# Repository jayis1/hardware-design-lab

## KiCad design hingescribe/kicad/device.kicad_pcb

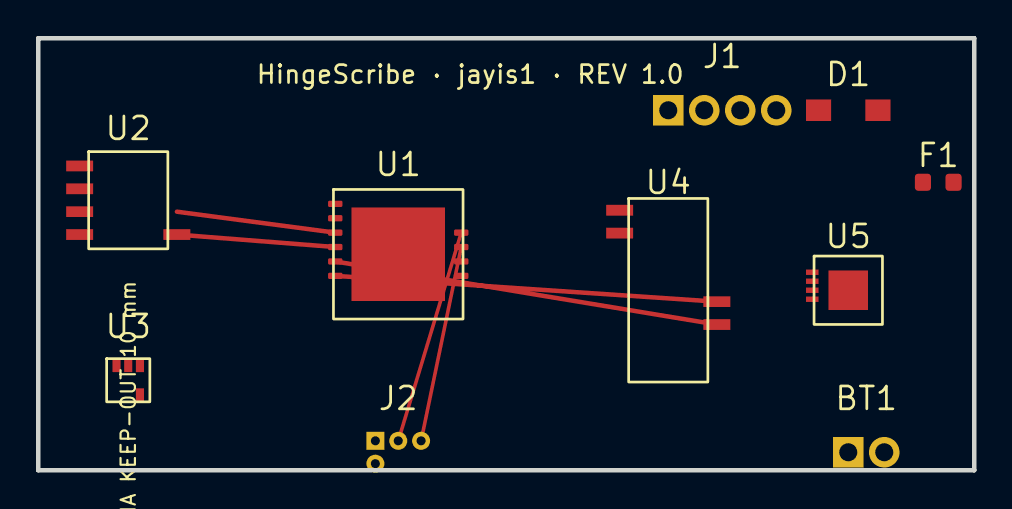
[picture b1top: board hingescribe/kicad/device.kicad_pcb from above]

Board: 4 copper layers, 52.0 x 24.0 mm, 10 parts (0 on the bottom side), 11 nets.

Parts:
BT1: LIPO_300mAh_PROTECTED; JST_PH_S2B-PH-K_1x02_P2.00mm_Horizontal
D1: MBR0520LT1G_BRIDGE; D_SOD-123
F1: PTC_100mA; Fuse_0603_1608Metric
J1: LOAD_CELL; JST_PH_S4B-PH-K_1x04_P2.00mm_Horizontal
J2: SWD_TAG_CONNECT; Tag-Connect_TC2030-IDC-NL_2x03_P1.27mm_Vertical
U1: nRF52840-QIAA; QFN-73-1EP_7x7mm_P0.4mm_EP5.2x5.2mm
U2: AS5600-ASOT; SOIC-8_3.9x4.9mm_P1.27mm
U3: TMP117MAIDRVR; WSON-6_2x2mm_P0.65mm
U4: HX711; SOIC-16_3.9x9.9mm_P1.27mm
U5: BQ25570RGRR; VQFN-20-1EP_3.5x3.5mm_P0.5mm_EP2.2x2.2mm

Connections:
3V3: J1.1, J2.1, U1.1, U2.1, U3.1, U4.1, U5.4
ANGLE_ALERT: U1.9, U2.5
GND: BT1.2, D1.2, J1.4, J2.3, U1.2, U1.73, U2.2, U3.2, U4.2, U5.2, U5.21
HARVEST_DC: D1.1, F1.1, U5.1
I2C_SCL: U1.4, U2.4, U3.4
I2C_SDA: U1.3, U2.3, U3.3
LOAD_DOUT: J1.2, U1.5, U4.11
LOAD_SCK: J1.3, U1.6, U4.12
SWCLK: J2.4, U1.8
SWDIO: J2.2, U1.7
VBAT: BT1.1, F1.2, U5.3

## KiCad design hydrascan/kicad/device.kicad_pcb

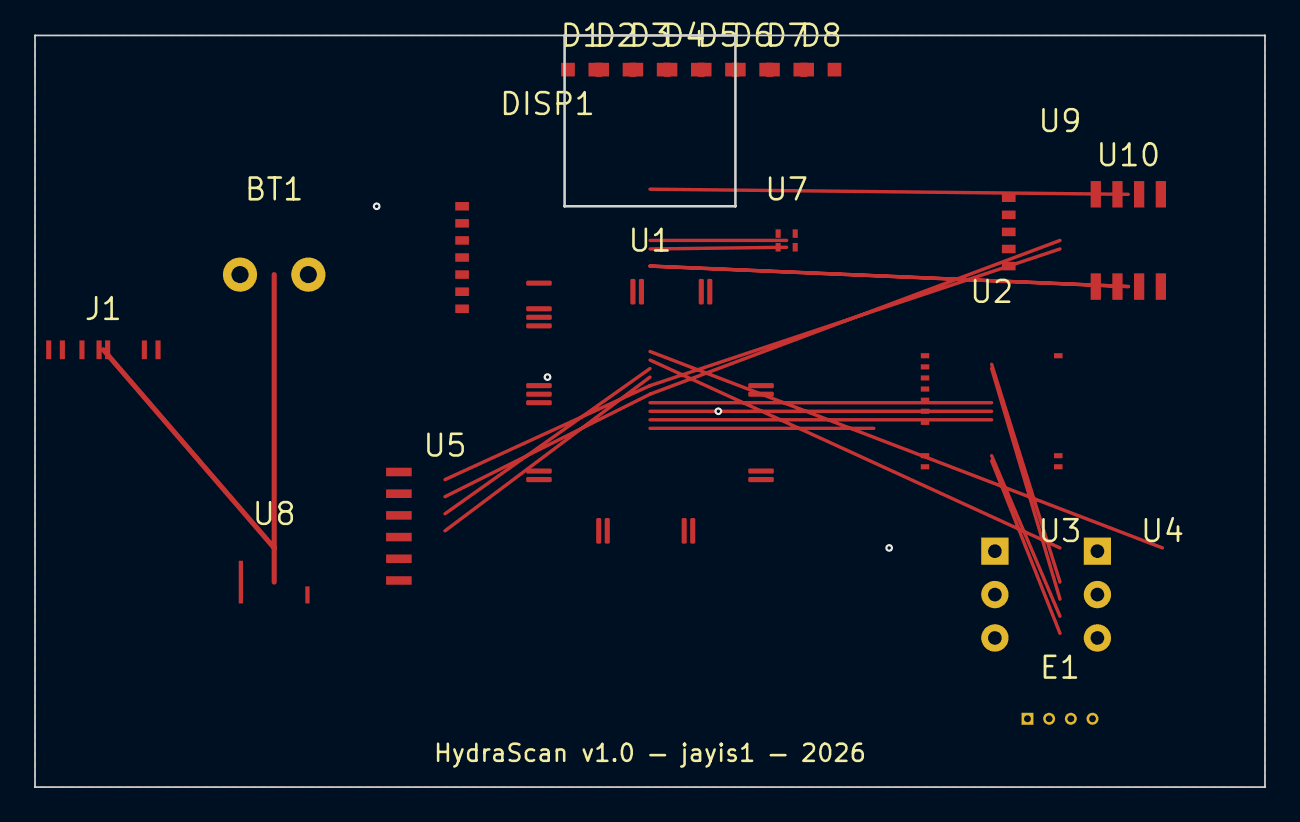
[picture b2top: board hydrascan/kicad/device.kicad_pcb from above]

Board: 4 copper layers, 72.0 x 44.0 mm, 21 parts (0 on the bottom side), 26 nets.

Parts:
BT1: LiPo_600mAh; BatteryHolder_Keystone_1042_18650
D1: LED_255nm; LED_0603_1608Metric
D2: LED_280nm; LED_0603_1608Metric
D3: LED_365nm; LED_0603_1608Metric
D4: LED_470nm; LED_0603_1608Metric
D5: LED_590nm; LED_0603_1608Metric
D6: LED_660nm; LED_0603_1608Metric
D7: LED_850nm; LED_0603_1608Metric
D8: LED_940nm; LED_0603_1608Metric
DISP1: SSD1306_128x64; SSD1306_0.96in_SPI
E1: IDE_4wire_316L; PinHeader_1x04_P1.27mm_Vertical
J1: USB-C; USB_C_Receptacle_HRO_TYPE-C-31-M-12
U1: STM32H733VGTx; LQFP-100_14x14mm_P0.5mm
U2: AD5940BCCZ; SSOP-28_5.3x10.2mm_P0.65mm
U3, U4: OPT101; DIP-8_W7.62mm
U5: 74HC595; SOIC-16_3.9x9.9mm_P1.27mm
U7: TMP117; SON-6_1.5x1.5mm_P0.5mm
U8: BQ25895; QFN-24-1EP_4x4mm_P0.5mm_EP2.7x2.7mm
U9: ANNA-B112
U10: W25Q64JV; SOIC-8_5.27x5.27mm_P1.27mm

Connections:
AD5940_IRQ: U1.21, U2.6
ADC_REF_PD: U1.61, U4.2
ADC_SAMPLE_PD: U1.60, U3.2
BLE_RX: U1.12, U9.2
BLE_TX: U1.11, U9.1
EIS_RC0: E1.1, U2.10
EIS_RC1: E1.2, U2.11
EIS_SE0: E1.3, U2.12
EIS_SE1: E1.4, U2.13
GND: BT1.2, D1.2, D2.2, D3.2, D4.2, D5.2, D6.2, D7.2, D8.2, DISP1.2, J1.A1, J1.A5, J1.B12, U1.1, U1.100, U2.1, U3.3, U4.3, U7.3, U9.4, U10.4
I2C_SCL: U1.30, U7.1, U8.20
I2C_SDA: U1.31, U7.2, U8.21
LED_MUX_LATCH: U1.80, U5.4
LED_MUX_MOSI: U1.71, U5.2
LED_MUX_SCK: U1.70, U5.3
LED_OE_N: U1.81, U5.6
QSPI_CLK: U1.51, U10.6
QSPI_CS: U1.50, U10.1
SPI2_CS: U1.20, U2.2
SPI2_SCK: U1.3, U2.3
USB_DM: J1.A6, U1.40
USB_DP: J1.A7, U1.41
VBAT: BT1.1, U8.10
VBUS: J1.A4, J1.B9, U8.1, U8.2
VCC: DISP1.1, U1.2, U2.28, U3.1, U4.1, U7.4, U9.3, U10.8
VDD_LED: D1.1, D2.1, D3.1, D4.1, D5.1, D6.1, D7.1, D8.1, U5.1, U5.5

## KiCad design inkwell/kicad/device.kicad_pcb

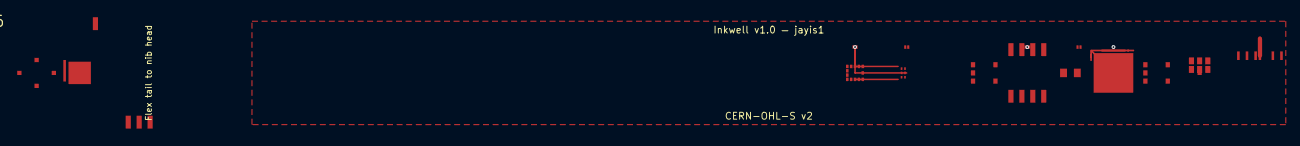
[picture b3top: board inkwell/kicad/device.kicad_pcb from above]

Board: 4 copper layers, 17 parts (0 on the bottom side), 12 nets.

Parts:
AE1: 2.4GHz Chip; Texas_SWRA117D_2.4GHz
C2, C3, C4, C5: 100nF; C_0402_1005Metric
J1: USB-C 2.0; USB_C_Receptacle_HRO_TYPE-C-31-M-12
SG1: 350Ω Full Bridge; StrainGauge_5mm
U1: nRF52833-QFAA; QFN-48-1EP_6x6mm_P0.4mm_EP4.6x4.6mm
U2: BMI270; LGA-14_2.5x3mm_P0.5mm
U3: BMM150; LGA-12_2x2mm_P0.5mm
U4: PMW3360; QFN-24-1EP_4x4mm_P0.5mm_EP2.6x2.6mm
U5: W25Q64JVSIQ; SOIC-8_3.9x4.9mm_P1.27mm
U6: HX711; SOIC-16_3.9x9.9mm_P1.27mm
U7: MAX17048; SOT-23-8
U8: MCP73831T-2ACI; SOT-23-5
U9: TPS7A4001; SOT-23-5
Y1: 32.768kHz; Crystal_SMD_3215-2Pin_3.2x1.5mm

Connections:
ANT_RF: AE1.1, U1.48
GND: C2.2, C3.2, C4.2, C5.2, J1.A1, J1.B1, SG1.2, SG1.4, U1.2, U1.8, U1.9, U1.EP, U2.2, U2.3, U2.6, U2.12, U2.13, U2.14, U3.2, U4.EP, U5.4, U7.2, U8.3, U9.2, U9.5
HX_DOUT: SG1.3, U6.14
SPI0_MISO: U2.9, U3.6
SPI0_MOSI: U2.10, U3.4
SPI0_SCK: U2.8, U3.5
VBAT: SG1.1, U6.1, U7.5, U7.6, U8.4
VBUS: J1.A4, J1.B4, U8.1, U8.5
VDD_1V8: C3.1, C4.1, U1.10, U1.11, U2.1, U2.4, U2.11, U3.1, U9.3
VDD_3V3: C2.1, C5.1, U1.1, U1.3, U1.6, U1.7, U5.3, U5.7, U5.8, U6.16, U7.1, U9.1, U9.4
XL1: U1.4, Y1.1
XL2: U1.5, Y1.2

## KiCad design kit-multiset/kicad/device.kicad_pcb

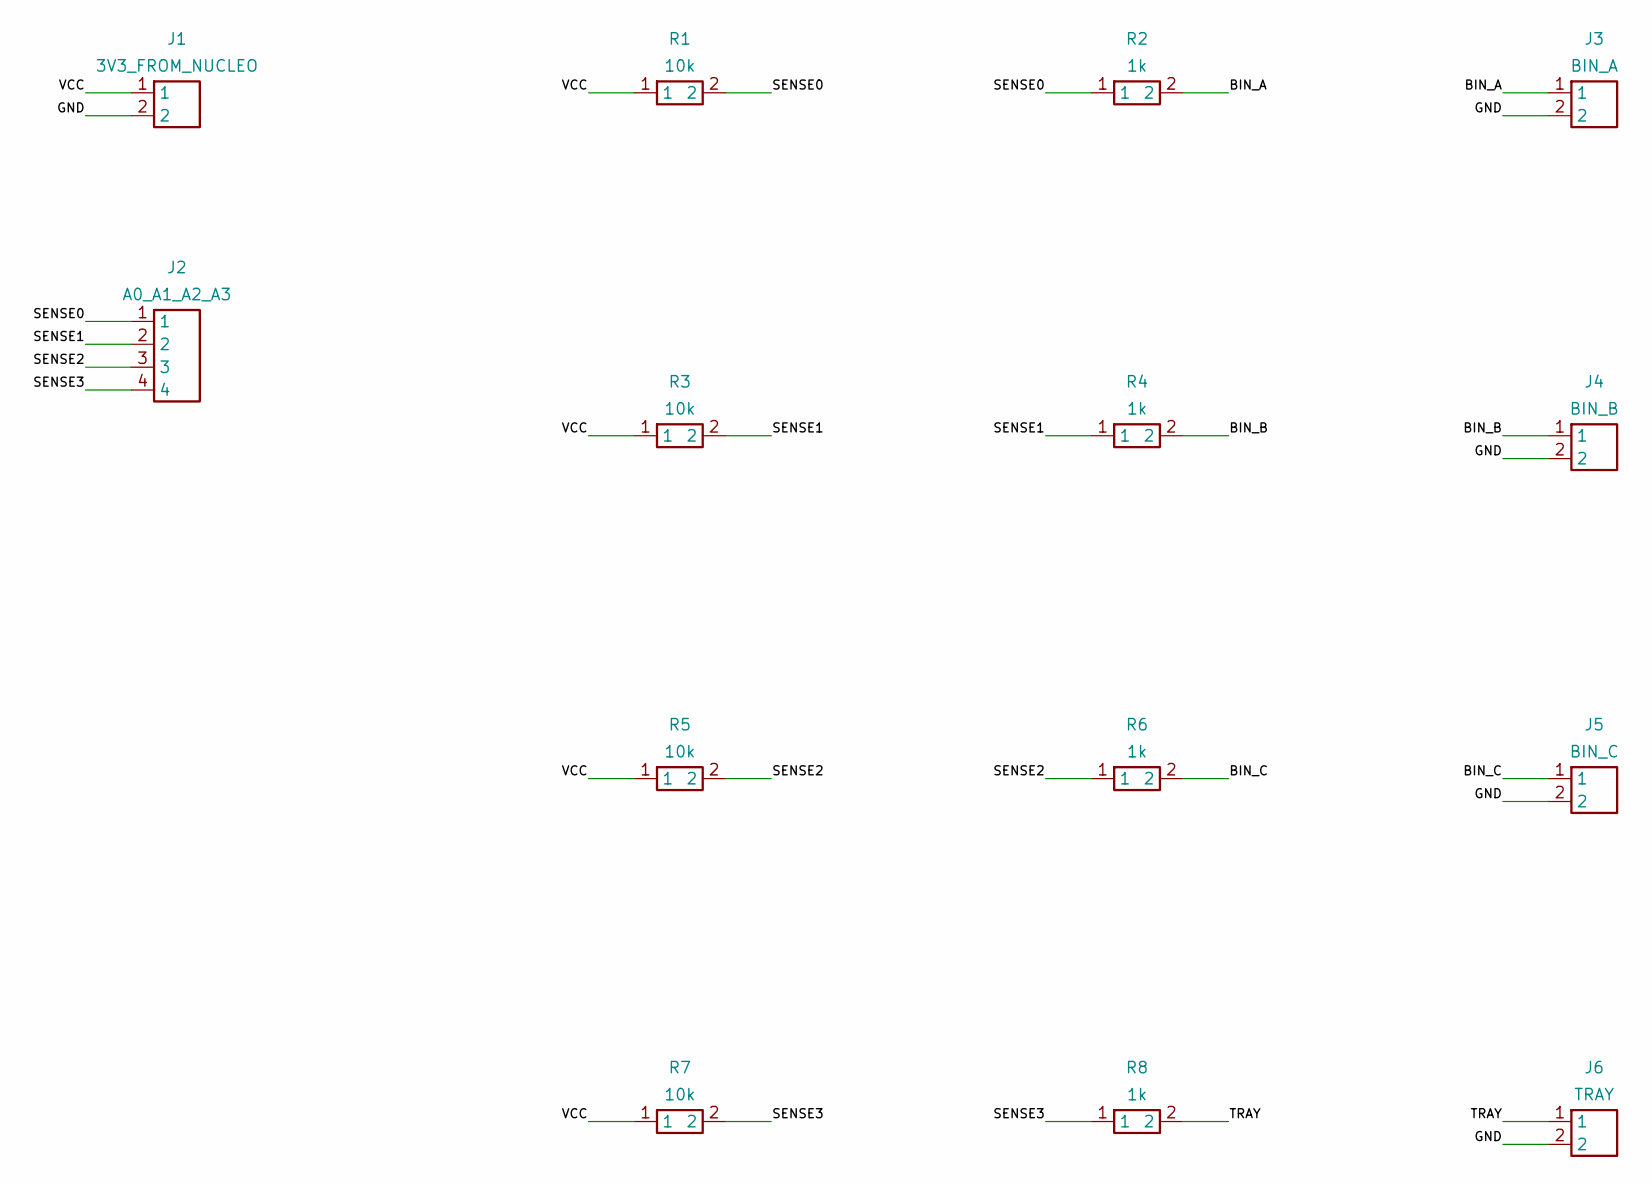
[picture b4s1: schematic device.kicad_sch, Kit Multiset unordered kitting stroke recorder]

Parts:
J1: 3V3_FROM_NUCLEO; PinHeader_1x02_P2.54mm_Vertical
J2: A0_A1_A2_A3; PinHeader_1x04_P2.54mm_Vertical
J3: BIN_A; PinHeader_1x02_P2.54mm_Vertical
J4: BIN_B; PinHeader_1x02_P2.54mm_Vertical
J5: BIN_C; PinHeader_1x02_P2.54mm_Vertical
J6: TRAY; PinHeader_1x02_P2.54mm_Vertical
R1, R3, R5, R7: 10k; R_Axial_DIN0207_L6.3mm_D2.5mm_P7.62mm_Horizontal
R2, R4, R6, R8: 1k; R_Axial_DIN0207_L6.3mm_D2.5mm_P7.62mm_Horizontal

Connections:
BIN_A: J3.1, R2.2
BIN_B: J4.1, R4.2
BIN_C: J5.1, R6.2
GND: J1.2, J3.2, J4.2, J5.2, J6.2
SENSE0: J2.1, R1.2, R2.1
SENSE1: J2.2, R3.2, R4.1
SENSE2: J2.3, R5.2, R6.1
SENSE3: J2.4, R7.2, R8.1
TRAY: J6.1, R8.2
VCC: J1.1, R1.1, R3.1, R5.1, R7.1

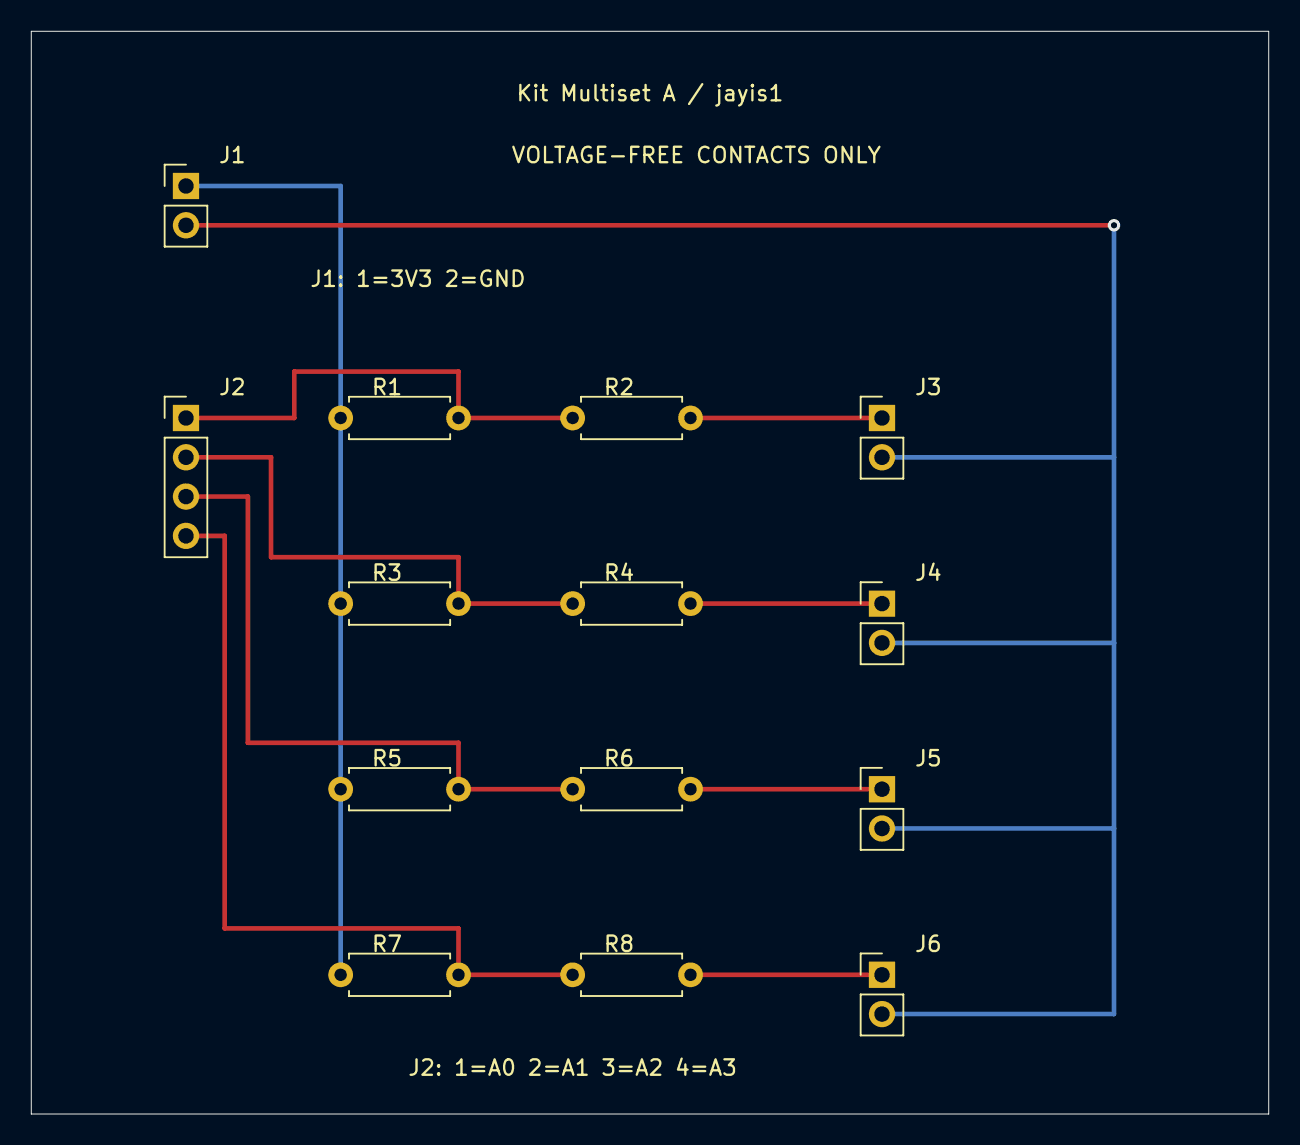
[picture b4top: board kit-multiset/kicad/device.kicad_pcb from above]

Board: 2 copper layers, 80.0 x 70.0 mm, 14 parts (0 on the bottom side), 10 nets.

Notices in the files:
hivevox/kicad/device.kicad_sch:
MIT License
hydrascan/kicad/device.kicad_pcb:
Author: jayis1 — Copyright (C) 2026 jayis1
4-layer, 72x44 mm, CERN-OHL-S v2
hydrascan/kicad/device.kicad_sch:
CERN-OHL-S v2 / GPL-3.0 / MIT
hydrofluor/kicad/device.kicad_sch:
Author: jayis1  License: MIT
inkwell/kicad/device.kicad_pcb:
CERN-OHL-S v2
inkwell/kicad/device.kicad_sch:
Author: jayis1 — Copyright (C) 2026 jayis1 — CERN-OHL-S v2
